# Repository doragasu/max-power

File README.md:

# max-power: Multi ATX Cross Power

This is just a dumb PCB that I designed to end with the big mess of wall adapters I have under my TV, powering two RaspberryPi boards, several hard disks, routers, a USB hub, an HDMI to optical splitter, and maybe something more I'm missing right now. The board provides the following outputs:

* 2x5V standby (USB-A, always ON)
* 4x5V (USB-A)
* 6x12V (Terminal blocks)
* 4x3.3V (Terminal blocks)

It also features a power button and a power LED.

## Usage

The board must be connected at least to an ATX power source (I use a very old 300W one) and to a Raspberry Pi (that will be always powered, I connect the one I use as home server). This RPi is connected to an internal ATX +5V_SB rail, so as long as the ATX PS is powered, so will be this RPi. To power ON/OFF all the power outputs (other than the +5V_SB ones), a small program on the RPi monitors:
* The power button on the board; and
* The network for specially crafted packets.

This way the PS can be switched ON/OFF either by pressing the power button, or by using an application (e.g. on a smartphone) to send power ON/OFF commands.

## Licenses

Footprints and 3D modules under `fp` directory, have been obtained from http://smisioto.no-ip.org/elettronica/kicad/kicad-en.htm, and are under GPLv3 license. All other hardware CAD files in this repository are licensed under the CERN OHL 1.2 license.

Software sources under this repository are licensed under the GPLv3+ license.

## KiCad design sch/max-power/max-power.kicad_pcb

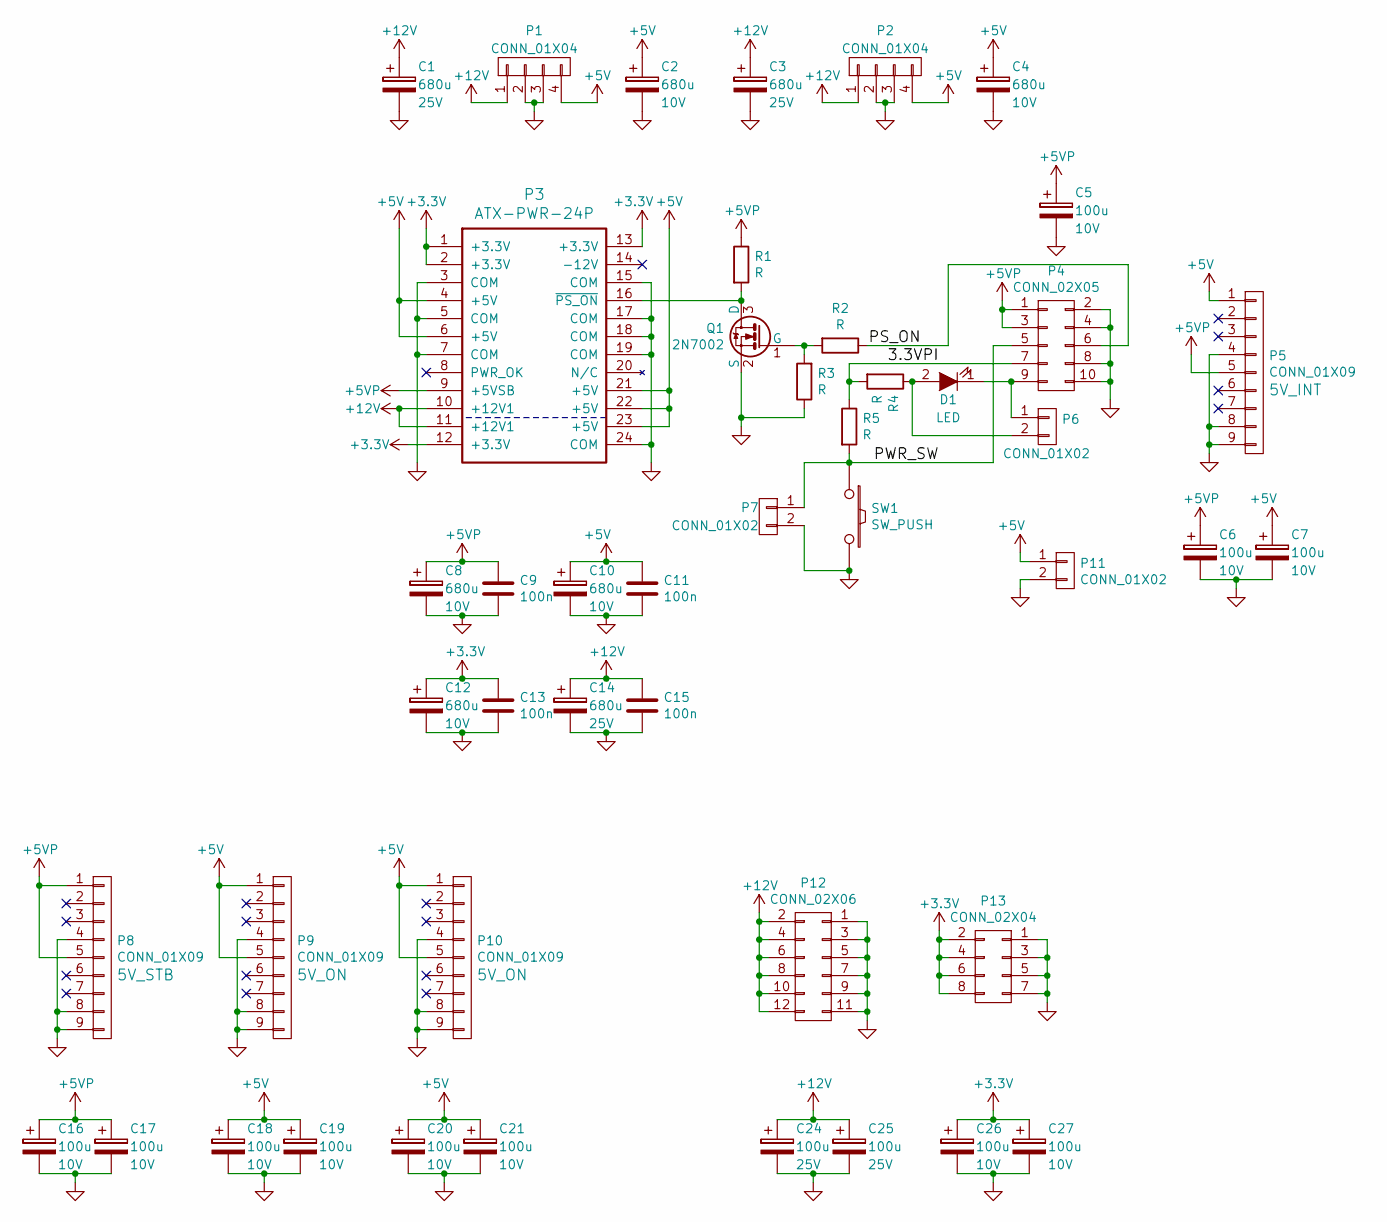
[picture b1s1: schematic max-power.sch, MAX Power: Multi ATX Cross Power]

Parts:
C1, C3, C14: 680u; C_Radial_D10_L13_P5; Rating 25V
C2, C4, C8, C10, C12: 680u; C_Radial_D10_L13_P5; Rating 10V
C5, C6, C7, C16, C17, C18, C19, C20, C21, C26, C27: 100u; C_Radial_D5_L11_P2; Rating 10V
C9, C11, C13, C15: 100n; C_0805
C24, C25: 100u; C_Radial_D5_L11_P2; Rating 25V
D1: LED; LED-5MM
P1, P2: CONN_01X04; conn_hdd_15-24-4449
P3: ATX-PWR-24P; ATX_PWR_CON
P4: CONN_02X05; IDC_Header_Straight_10pins
P5, P8, P9, P10: CONN_01X09; USB_A_STACKED
P6, P7: CONN_01X02; Socket_MOLEX-KK-RM2-54mm_Lock_2pin_straight
P11: CONN_01X02; Socket_MOLEX-KK-RM3-96mm_Lock_2pin_straight
P12: CONN_02X06; TERM_BLOCK_6x2_5.08
P13: CONN_02X04; TERM_BLOCK_4x2_5.08
Q1: 2N7002; SOT-23
R1, R2, R3, R4, R5: R; R_0805
SW1: SW_PUSH; SW_PUSH_SMALL

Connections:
+3V3: C12.1, C13.1, C26.1, C27.1, P3.1 (+3.3V), P3.2 (+3.3V), P3.12 (+3.3V), P3.13 (+3.3V), P13.2, P13.4, P13.6, P13.8
+5V: C2.1, C4.1, C7.1, C10.1, C11.1, C18.1, C19.1, C20.1, C21.1, P1.4, P2.4, P3.4 (+5V), P3.6 (+5V), P3.21 (+5V), P3.22 (+5V), P3.23 (+5V), P5.1, P9.1, P9.5, P10.1, P10.5, P11.1
+5VP: C5.1, C6.1, C8.1, C9.1, C16.1, C17.1, P3.9 (+5VSB), P4.1, P4.3, P5.5, P8.1, P8.5, R1.1
+12V: C1.1, C3.1, C14.1, C15.1, C24.1, C25.1, P1.1, P2.1, P3.10 (+12V1), P3.11 (+12V1), P12.2, P12.4, P12.6, P12.8, P12.10, P12.12
/3.3VPI: P4.7, R4.2, R5.1
/PS_ON: P4.6, R2.1
/PWR_SW: P4.5, P7.1, R5.2, SW1.1
GND: C1.2, C2.2, C3.2, C4.2, C5.2, C6.2, C7.2, C8.2, C9.2, C10.2, C11.2, C12.2, C13.2, C14.2, C15.2, C16.2, C17.2, C18.2, C19.2, C20.2, C21.2, C24.2, C25.2, C26.2, C27.2, P1.2, P1.3, P2.2, P2.3, P3.3 (COM), P3.5 (COM), P3.7 (COM), P3.15 (COM), P3.17 (COM), P3.18 (COM), P3.19 (COM), P3.24 (COM), P4.2, P4.4, P4.8, P4.10, P5.4, P5.8, P5.9, P7.2, P8.4, P8.8, P8.9, P9.4, P9.8, P9.9, P10.4, P10.8, P10.9, P11.2, P12.1, P12.3, P12.5, P12.7, P12.9, P12.11, P13.1, P13.3, P13.5, P13.7, Q1.2 (S), R3.1, SW1.2
unnamed: D1.1 (K), P4.9, P6.1
unnamed: D1.2 (A), P6.2, R4.1
unnamed: P3.16 (~PS_ON), Q1.3 (D), R1.2
unnamed: Q1.1 (G), R2.2, R3.2

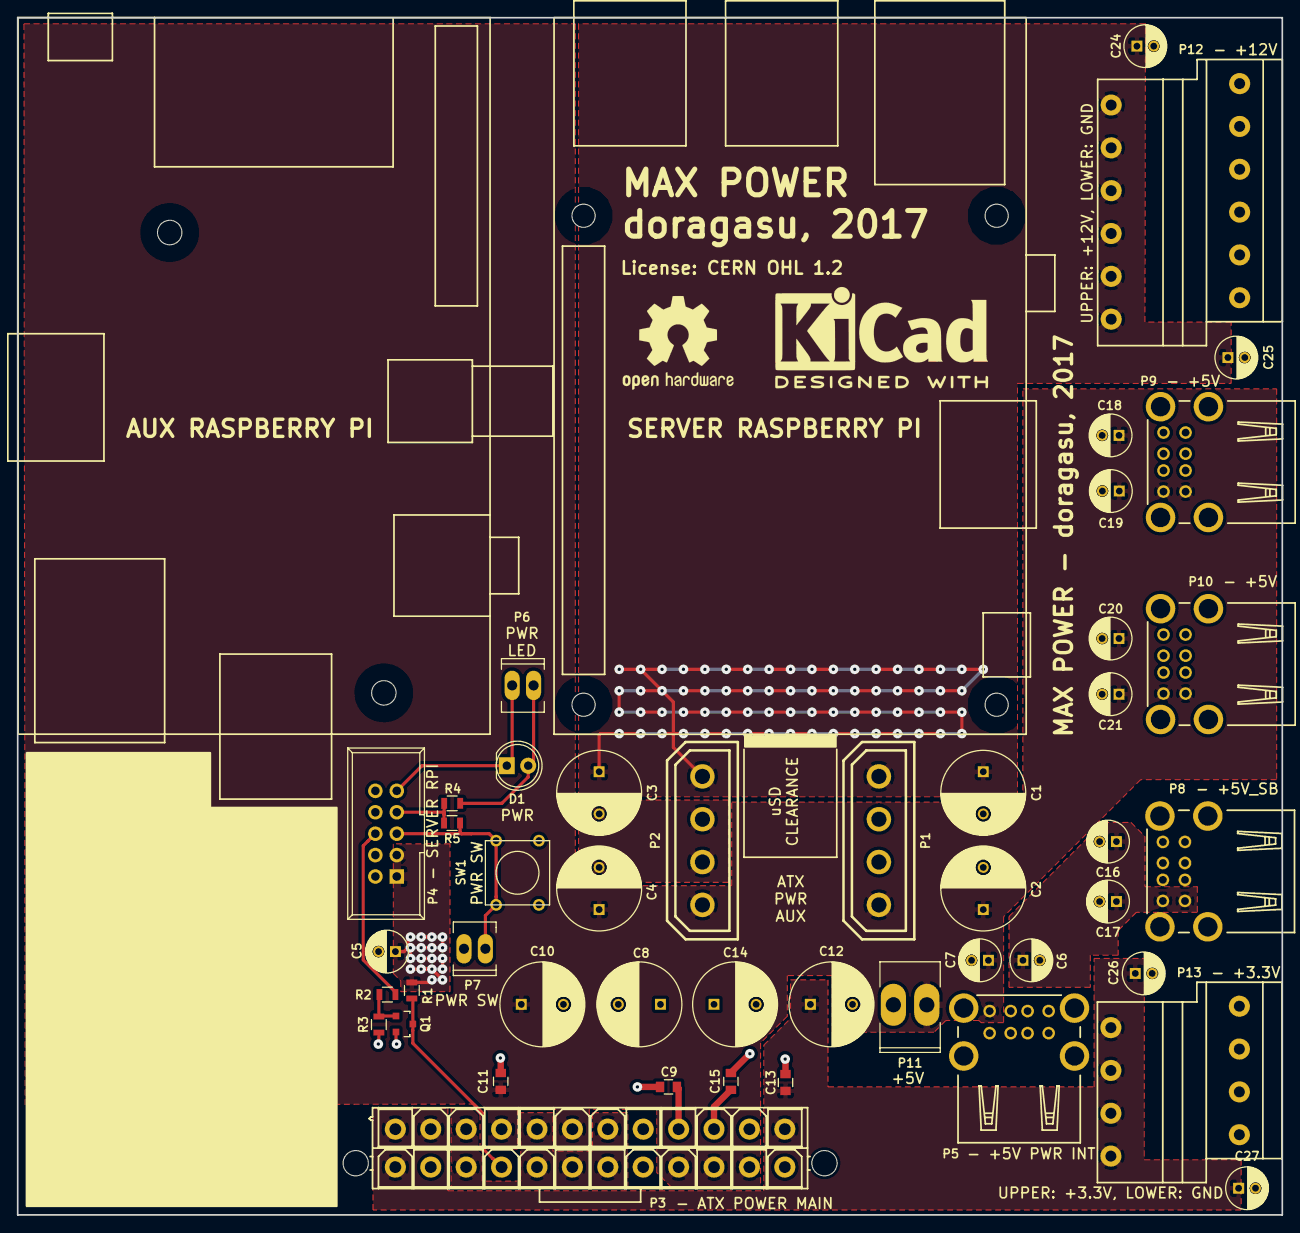
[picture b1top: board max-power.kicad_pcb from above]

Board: 2 copper layers, 150.0 x 142.0 mm, 46 parts (0 on the bottom side), 12 nets.

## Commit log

2017-01-07 Added files.
2017-01-07 Initial placement of footprints.
2017-01-08 Routed PCB.
2017-01-08 Stetic changes.
2017-02-05 Revision A finished, Gerbers sent to fab house.

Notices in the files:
sch/max-power/max-power.kicad_pcb:
License: CERN OHL 1.2
